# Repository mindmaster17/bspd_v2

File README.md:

# Team Petronarc GECT
# bspd_v1
# BSPD_V1 — Brake System Plausibility Device (Formula Imperial CV)

This repository contains the circuit design, schematics, and documentation for **BSPD_V1**, a low-cost and rule-compliant Brake System Plausibility Device (BSPD) designed for **Formula Imperial Combustion (CV)** vehicles using **mechanical throttle**.

---
|  | 3D view of the BSPD PCB assembly (component placement & enclosure layout) |

##  Overview

The **Brake System Plausibility Device (BSPD)** monitors the **Throttle Position Sensor (TPS)** and **Brake Pressure Sensor (BPS)** to detect unsafe driving conditions — specifically, **when the throttle is open beyond a limit while the brake is applied**.

If such a condition persists for more than a preset time (≈500 ms), the BSPD **opens the shutdown circuit**, cutting engine power (via the fuel pump or ECU relay).

This design follows the **Formula Imperial 2025 Rulebook (E.2.9)** guidelines for CV vehicles.

|  | Electrical schematic showing comparators, thresholds, latch, and relay driver stages |
---

##  Key Features

- ✅ **2 Analog Inputs** — Throttle (0–5 V) and Brake (0–5 V or 0–10 V)
- ✅ **Adjustable Thresholds** for both BPS and TPS (via onboard potentiometers)
- ✅ **Plausibility Delay:** ~0.5 s (adjustable via RC network)
- ✅ **Latch on Fault:** Once tripped, BSPD remains in fault state until the **Primary Master Switch (PMS)** is cycled
- ✅ **Onboard Indicators:** LEDs for Brake threshold, Throttle threshold, and Fault
- ✅ **12 V operation (8–24 V range)** with onboard 5 V regulation
- ✅ **Fail-Safe Relay Output:** Normally Closed (NC) relay for shutdown loop

---

## 🧩 How It Works

1. **TPS Comparator** checks if throttle > 10% (or > set threshold).
2. **BPS Comparator** checks if brake > set pressure (typically ≥ 30 bar).
3. Both outputs go into a **NOR gate** — if both are HIGH (throttle + brake), output triggers fault.
4. A **delay comparator (≈500 ms)** ensures it’s not a false transient.
5. **Relay driver** drops the shutdown loop (fuel pump / ECU power).
6. BSPD stays tripped until **PMS is turned OFF → ON**.

---

## 🪛 Modifications (for FI 2025 Compliance)

| Issue | Action Taken | Rule Reference |
|-------|---------------|----------------|
| Auto reset after 10 s (non-compliant) | Disabled RC network (R12–C7) | FI E.2.9.5 |
| Cockpit reset not allowed | Only resets via PMS cycle | FI E.2.9.6 |
| Power always ON | BSPD powered only from PMS-switched 12 V line | FI E.2.9 |
| Plausibility logic | Verified 0.45 V – 5 V window check and 500 ms delay | FI E.2.9 |

---

## 🧰 Components

| Component | Value | Description |
|------------|--------|-------------|
| LM393 | Dual comparator | Plausibility & fault logic |
| LM7805 / LM2596 | Regulator | 12 V → 5 V logic supply |
| R12 | 100 kΩ | *Removed* to disable auto-reset |
| C7 | 100 µF | *Removed* or open-circuited |
| Relay | 12 V, SPDT, NC used for shutdown loop | Fuel/ECU cutoff |
| LEDs | — | Fault, TPS threshold, BPS threshold indicators |

---

## ⚡ Power & Wiring

```text
Battery +  → Primary Master Switch (PMS)  → Fuse  → BSPD +12 V  → Fuel Pump Relay Coil → ECU

BSPD Signal Output  →  Controls Shutdown Relay  → In series with Fuel Pump or ECU power

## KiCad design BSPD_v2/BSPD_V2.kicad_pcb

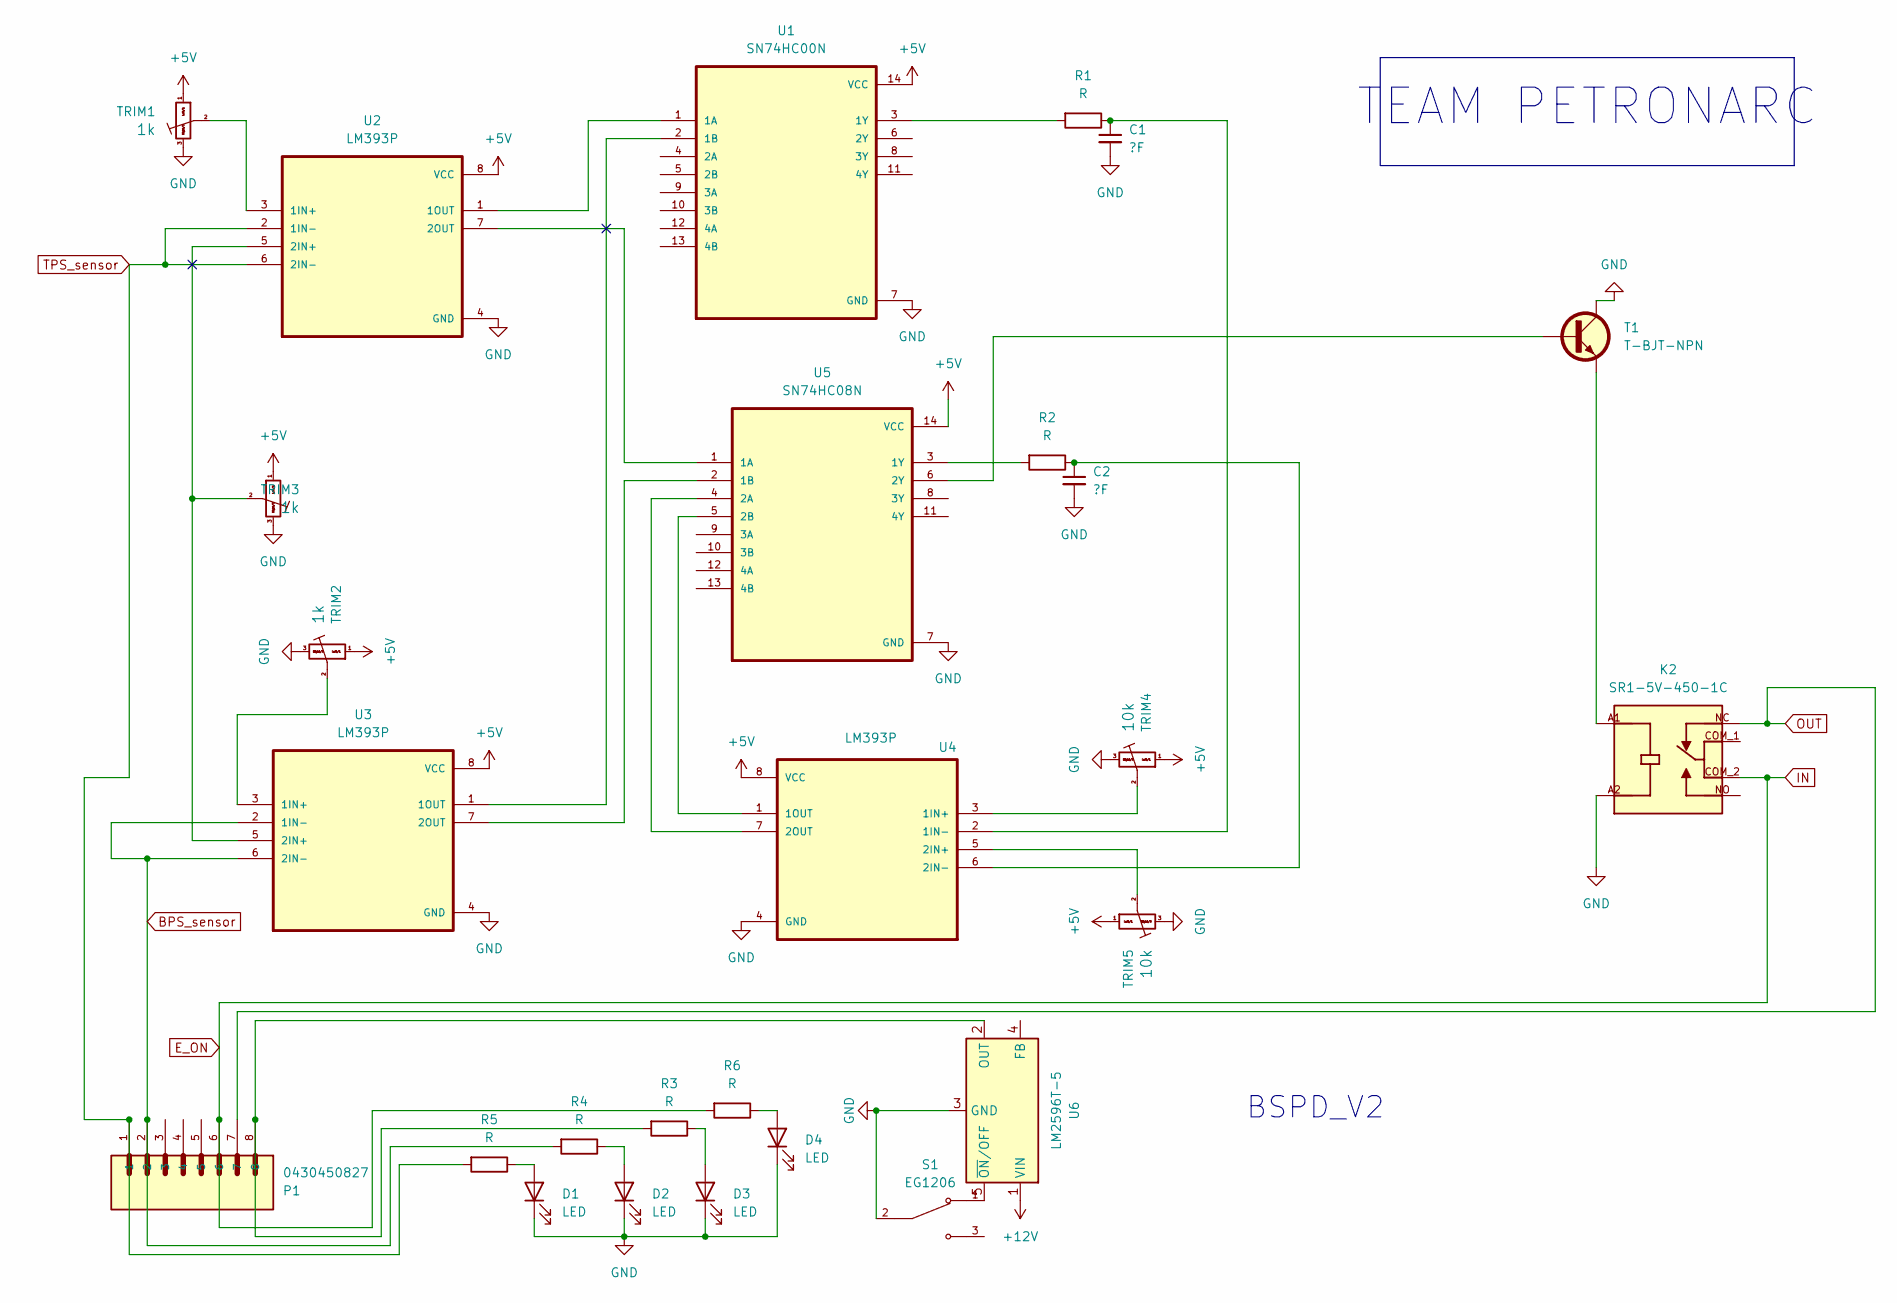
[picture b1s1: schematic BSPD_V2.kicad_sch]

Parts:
C1, C2: C_Generic; C_Disc_D12.5mm_W5.0mm_P10.00mm
D1, D2, D3, D4: LED; LED_D5.0mm_Horizontal_O6.35mm_Z9.0mm
K2: SR1-5V-450-1C; RELAY_SR1-5V-450-1C; PARTREV 1.01; DigiKey_Part_Number 2223-SR1-5V-450-1C-ND
P1: 0430450827; Molex_Mega-Fit_76825-0008_2x04_P5.70mm_Horizontal
R1, R2, R3, R4, R5, R6: R; R_Axial_DIN0204_L3.6mm_D1.6mm_P2.54mm_Vertical
S1: EG1206; SW_E-Switch_EG1224_SPDT_Angled; PARTREV B
T1: T-BJT-NPN; TO-92L_ECB
TRIM1: TrimPot_TC33X_1k; Potentiometer_Bourns_3296W_Vertical; Part Number TC33X-2-102G
TRIM2, TRIM3: TrimPot_T73YEt_1k; Potentiometer_Bourns_3296W_Vertical; Part Number T73YE102KT20
TRIM4, TRIM5: TrimPot_T73YEt_10k; Potentiometer_Bourns_3296W_Vertical; Part Number T73YE102KT20
U1: SN74HC00N; DIP-14_W7.62mm
U2, U3, U4: LM393P; DIP-8_W7.62mm
U5: SN74HC08N; DIP-14_W7.62mm; DigiKey_Part_Number 2156-SN74HC08N-ND
U6: LM2596T-5; TO-220F-5_P3.4x2.06mm_StaggerEven_Lead1.86mm_Vertical

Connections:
+5V: TRIM1.1 (Left), TRIM2.1 (Left), TRIM3.1 (Left), TRIM4.1 (Left), TRIM5.1 (Left), U1.14 (VCC), U2.8 (VCC), U3.8 (VCC), U4.8 (VCC), U5.14 (VCC)
+12V: U6.1 (VIN)
BPS_sensor: P1.2, R4.2, U3.2 (1IN-), U3.6 (2IN-)
E_ON: K2.COM_2, P1.6, R6.2
GND: C1.2, C2.2, D1.1 (K), D2.1 (K), D3.1 (K), D4.1 (K), K2.A2, S1.2, T1.1 (C), TRIM1.3 (Right), TRIM2.3 (Right), TRIM3.3 (Right), TRIM4.3 (Right), TRIM5.3 (Right), U1.7 (GND), U2.4 (GND), U3.4 (GND), U4.4 (GND), U5.7 (GND), U6.3 (GND)
unnamed: D1.2 (A), R5.1
unnamed: D2.2 (A), R4.1
unnamed: D3.2 (A), R3.1
unnamed: D4.2 (A), R6.1
unnamed: T1.2 (B), U5.6 (2Y)
unnamed: K2.A1, T1.3 (E)
unnamed: TRIM1.2 (Center), U2.3 (1IN+)
unnamed: TRIM2.2 (Center), U3.3 (1IN+)
unnamed: TRIM3.2 (Center), U2.5 (2IN+), U3.5 (2IN+)
unnamed: TRIM4.2 (Center), U4.3 (1IN+)
unnamed: TRIM5.2 (Center), U4.5 (2IN+)
unnamed: U1.1 (1A), U2.1 (1OUT)
unnamed: U1.2 (1B), U3.1 (1OUT)
unnamed: R1.2, U1.3 (1Y)
unnamed: U2.7 (2OUT), U5.1 (1A)
unnamed: U3.7 (2OUT), U5.2 (1B)
unnamed: C1.1, R1.1, U4.2 (1IN-)
unnamed: U4.1 (1OUT), U5.5 (2B)
unnamed: C2.1, R2.1, U4.6 (2IN-)
unnamed: U4.7 (2OUT), U5.4 (2A)
unnamed: R2.2, U5.3 (1Y)
unnamed: P1.8, R3.2, U6.2 (OUT)
unnamed: S1.1, U6.5 (~ON/OFF)
OUT: K2.NC, P1.7
TPS_sensor: P1.1, R5.2, U2.2 (1IN-), U2.6 (2IN-)

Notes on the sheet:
BSPD_V2
TEAM PETRONARC

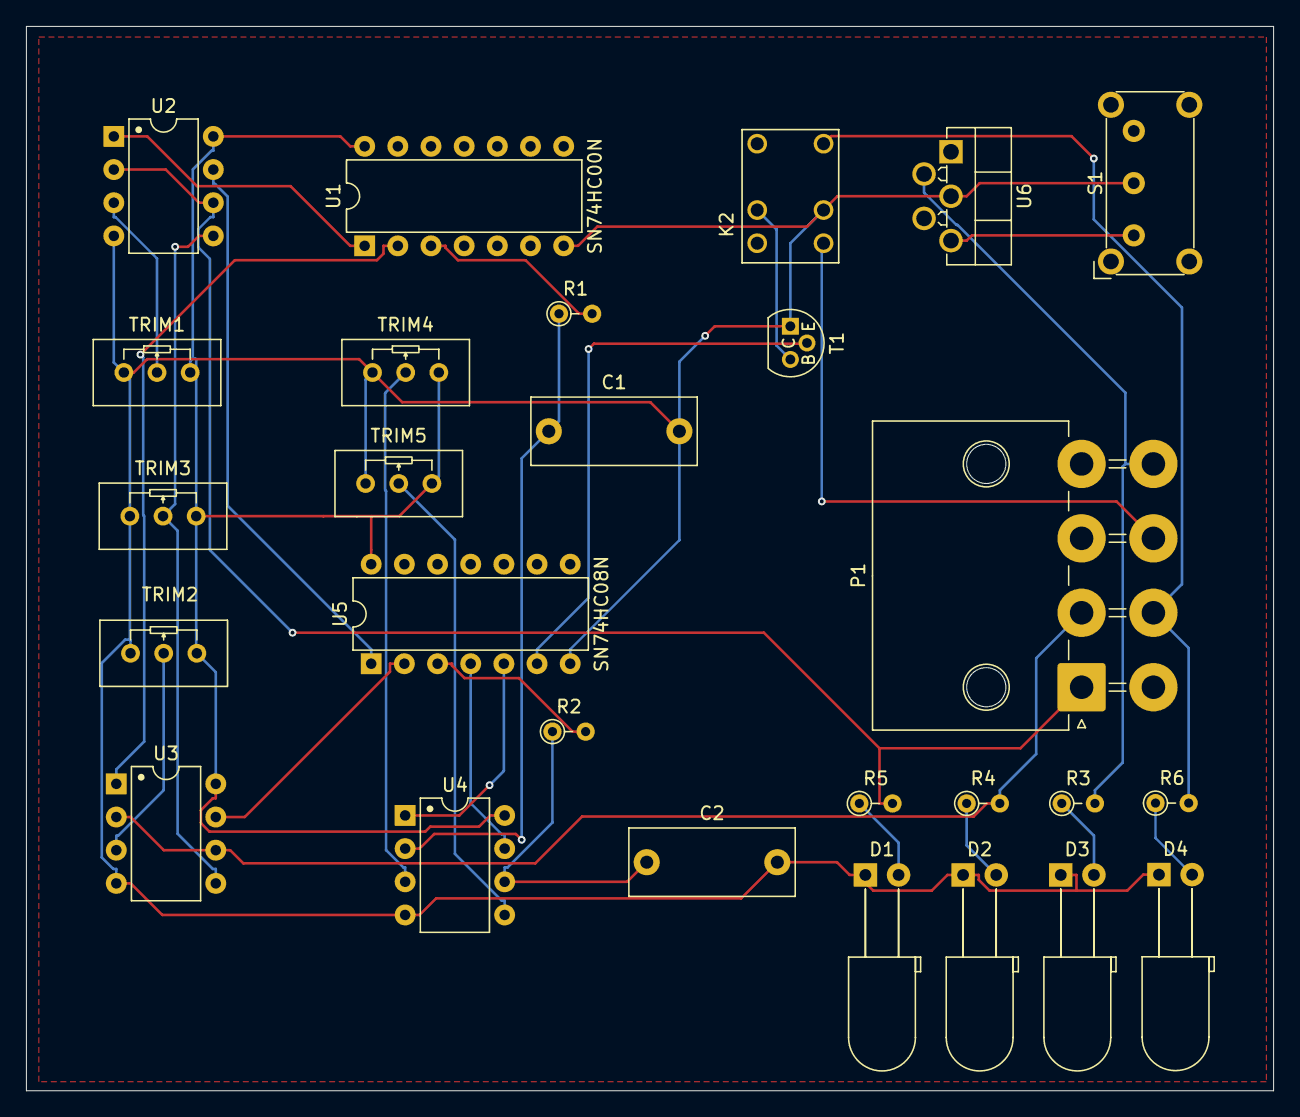
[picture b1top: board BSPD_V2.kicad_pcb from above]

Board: 2 copper layers, 95.5 x 81.5 mm, 27 parts (0 on the bottom side), 29 nets.

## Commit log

2025-09-28 updated kicad files
2025-09-28 added logic files
2025-09-28 updated schematic
2025-09-28 updated library
2025-09-28 updated footprints
2025-09-28 Updated images
2025-09-28 Added footprints
2025-09-28 Updated pcb design
2025-09-28 Updated pcb design with check
2025-09-28 pcb design updated using proper footprints and routing
2025-09-28 Added footprints for 5v Regulator
2025-09-28 pcd updated gerber file created
2025-09-29 update BSPD_v2_render
2025-10-20 Update formatting of LICENSE.md sections
2025-10-20 Fix formatting in LICENSE.md headings
2026-01-20 Revise README for BSPD_V1 project details
    Updated README to reflect project details for BSPD_V1, including overview, key features, modifications for compliance, components, and wiring.
